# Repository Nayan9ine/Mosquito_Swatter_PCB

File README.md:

<div align="center">Mosquito Swatter Circuit</div>
<br>
Objective: Reverse Engineered pcb design of a mosquito swatter circuit built using KiCad
<br><br>This is my first attempt at drawing a pcb and also using the KiCad software, so I have done the bare minimum of clearing Electrical Rules Checker and Design Rules Checker. There must be lots of routing and component placement issues but I have rounded up sharp edges and made the traces as short as possible.
<br><br>
<div align="center">
  
  <br><sub><i>Fig1:PCB Front</i></sub>
</div>
<br>
<div align="center">
  
  <sub><i>Fig2:PCB BACK</i></sub>
</div>
<br><br>
<div align="center">
  
  <br><sub><i>Fig3:Rough PCB sketch drawn directly by tracing</i></sub></div>
<br>
<div align="center">
  
  <br><sub><i>Fig4:Arranged</i></sub>
</div>
<br>
<div align="center">
 
 <br><sub><i>Fig5:PCB Editor</i></sub>
</div>
<br>
<div align="center">

<br><sub><i>Fig6:PCB Front</i></sub>
</div>
<br>
<div align="center">

<br><sub><i>Fig7:PCB Back</i></sub>
</div>

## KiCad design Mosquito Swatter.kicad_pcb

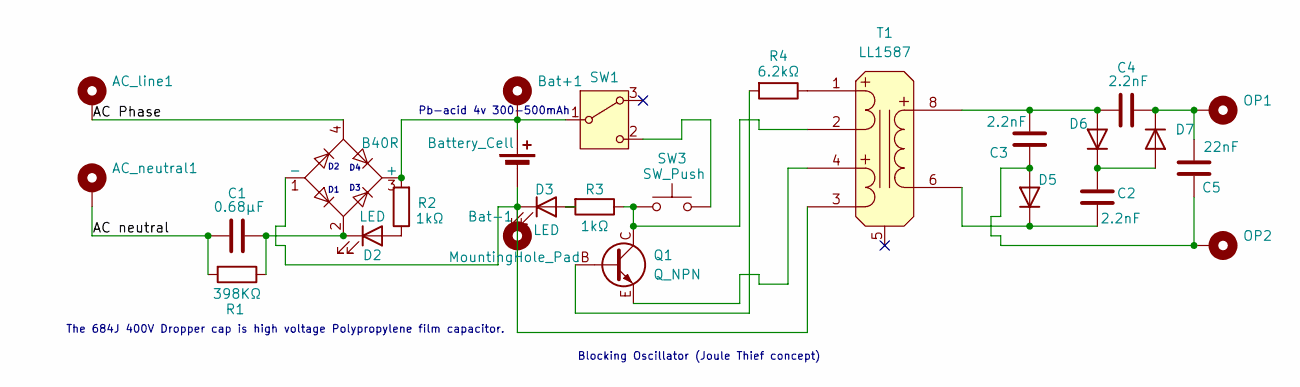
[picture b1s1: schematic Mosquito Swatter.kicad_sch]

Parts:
AC_line1: MountingHole_Pad; MountingHole_2.2mm_M2_DIN965_Pad
AC_neutral1: MountingHole_Pad; MountingHole_2.2mm_M2_DIN965_Pad
BT1: Battery_Cell
Bat+1: MountingHole_Pad; MountingHole_2.2mm_M2_DIN965_Pad
Bat-1: MountingHole_Pad; MountingHole_2.2mm_M2_DIN965_Pad
C1: 0.68µF; C_Rect_L24.0mm_W7.0mm_P22.50mm_MKT
C2, C3, C4: 2.2nF; CP_Radial_Tantal_D5.0mm_P5.00mm
C5: 22nF; C_Rect_L24.0mm_W7.0mm_P22.50mm_MKT
D1: B40R; Diode_Bridge_Round_D9.0mm
D2, D3: LED; LED_Rectangular_W3.0mm_H2.0mm
D5, D6, D7: S2JTR; D_5W_P12.70mm_Horizontal
OP1, OP2: MountingHole_Pad; MountingHole_2.2mm_M2_DIN965_Pad
Q1: Q_NPN; TO-126-3_Vertical
R1: 398KΩ; R_Axial_DIN0207_L6.3mm_D2.5mm_P10.16mm_Horizontal
R2, R3: 1kΩ; R_Axial_DIN0207_L6.3mm_D2.5mm_P10.16mm_Horizontal
R4: 6.2kΩ; R_Axial_DIN0207_L6.3mm_D2.5mm_P10.16mm_Horizontal
SW1: SW_Wuerth_450301014042; SW_Slide_SPDT_Angled_CK_OS102011MA1Q
SW3: SW_Push; SW_Tactile_SPST_Angled_PTS645Vx39-2LFS
T1: LL1587; Transformer_Breve_TEZ-22x24

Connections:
/AC Phase: AC_line1.1, D1.4
/AC neutral: AC_neutral1.1, C1.1, R1.1
unnamed: BT1.1 (+), Bat+1.1, D1.3 (+), R2.2, SW1.1 (B)
unnamed: BT1.2 (-), Bat-1.1, D1.1 (-), D3.1 (K), T1.3 (P2-)
unnamed: D2.2 (A), R2.1
unnamed: C1.2, D1.2, D2.1 (K), R1.2
unnamed: D3.2 (A), R3.2
unnamed: C3.2, C5.2, D5.2 (A), OP2.1
unnamed: C2.1, D5.1 (K), T1.6 (S-)
unnamed: C3.1, C4.1, D6.2 (A), T1.8 (S+)
unnamed: C2.2, D6.1 (K), D7.2 (A)
unnamed: C4.2, C5.1, D7.1 (K), OP1.1
unnamed: Q1.B, R4.2
unnamed: SW1.2 (C), SW3.2
unnamed: R4.1, T1.1 (P1+)
unnamed: Q1.C, R3.1, SW3.1, T1.2 (P1-)
unnamed: Q1.E, T1.4 (P2+)

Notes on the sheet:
Blocking Oscillator (Joule Thief concept)
The 684J 400V Dropper cap is high voltage Polypropylene film capacitor.
Pb-acid 4v 300-500mAh

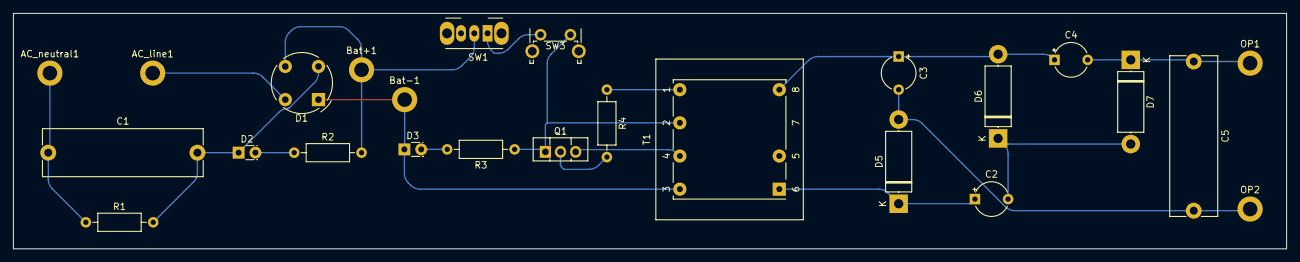
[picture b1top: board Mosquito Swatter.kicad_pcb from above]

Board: 2 copper layers, 192.0 x 35.5 mm, 25 parts (0 on the bottom side), 17 nets.
